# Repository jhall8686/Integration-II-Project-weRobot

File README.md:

# Integration-II-Project-weRobot
PCB FIles and Code for Autonomous Vehicle

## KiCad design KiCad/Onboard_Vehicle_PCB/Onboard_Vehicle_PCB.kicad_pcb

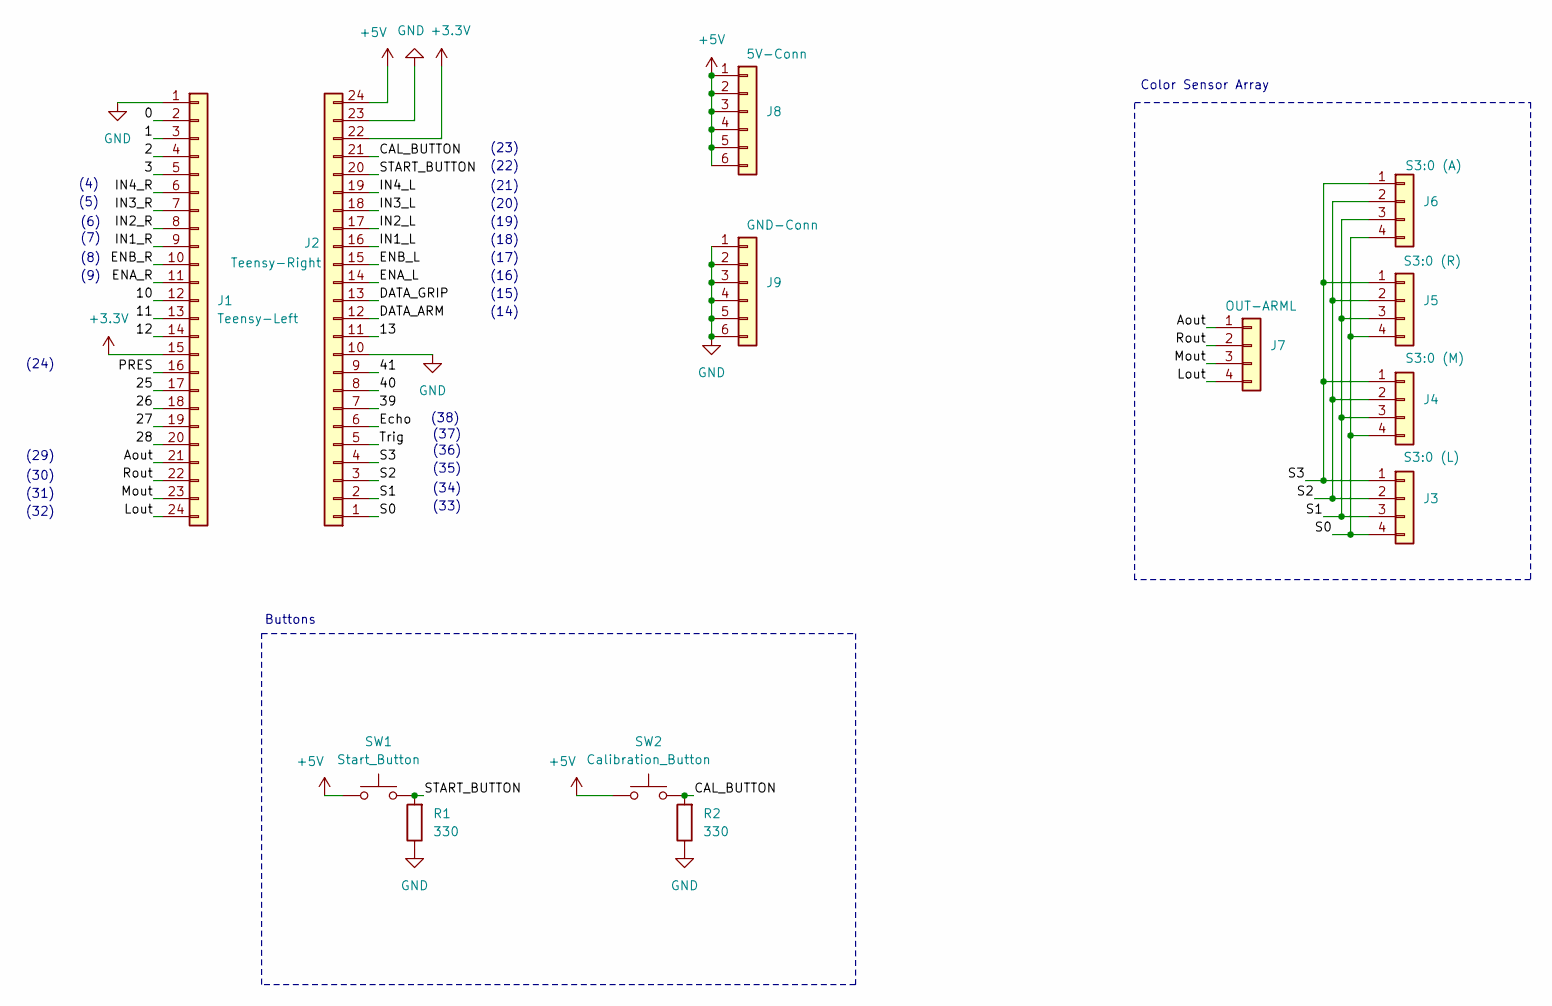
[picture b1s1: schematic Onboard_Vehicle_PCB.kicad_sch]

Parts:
J1: Teensy-Left; PinSocket_1x24_P2.54mm_Vertical
J2: Teensy-Right; PinSocket_1x24_P2.54mm_Vertical
J3: S3:0 (L); PinHeader_1x04_P2.54mm_Vertical
J4: S3:0 (M); PinHeader_1x04_P2.54mm_Vertical
J5: S3:0 (R); PinHeader_1x04_P2.54mm_Vertical
J6: S3:0 (A); PinHeader_1x04_P2.54mm_Vertical
J7: OUT-ARML; PinHeader_1x04_P2.54mm_Vertical
J8: 5V-Conn; PinHeader_1x06_P2.54mm_Vertical
J9: GND-Conn; PinHeader_1x06_P2.54mm_Vertical
R1, R2: 330; R_Axial_DIN0207_L6.3mm_D2.5mm_P10.16mm_Horizontal
SW1: Start_Button; SW_PUSH_6mm
SW2: Calibration_Button; SW_PUSH_6mm

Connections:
+3.3V: J1.15, J2.22
+5V: J2.24, J8.1, J8.2, J8.3, J8.4, J8.5, J8.6, SW1.1, SW2.1
/0: J1.2
/1: J1.3
/2: J1.4
/3: J1.5
/4: J1.6
/5: J1.7
/6: J1.8
/7: J1.9
/8: J1.10
/9: J1.11
/10: J1.12
/11: J1.13
/12: J1.14
/13: J2.11
/25: J1.17
/26: J1.18
/27: J1.19
/28: J1.20
/39: J2.7
/40: J2.8
/41: J2.9
/Aout: J1.21, J7.1
/CAL_BUTTON: J2.21, R2.2, SW2.2
/DATA_1: J2.12
/DATA_2: J2.13
/ENA: J2.14
/ENB: J2.15
/Echo: J2.6
/IN1: J2.16
/IN2: J2.17
/IN3: J2.18
/IN4: J2.19
/Lout: J1.24, J7.4
/Mout: J1.23, J7.3
/PRES: J1.16
/Rout: J1.22, J7.2
/S0: J2.1, J3.4, J4.4, J5.4, J6.4
/S1: J2.2, J3.3, J4.3, J5.3, J6.3
/S2: J2.3, J3.2, J4.2, J5.2, J6.2
/S3: J2.4, J3.1, J4.1, J5.1, J6.1
/START_BUTTON: J2.20, R1.2, SW1.2
/Trig: J2.5
GND: J1.1, J2.10, J2.23, J9.1, J9.2, J9.3, J9.4, J9.5, J9.6, R1.1, R2.1

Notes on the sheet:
(19)
(23)
(17)
(24)
(29)
(34)
(5)
(9)
(7)
(30)
(15)
(18)
Buttons
(36)
(33)
(6)
Color Sensor Array
(22)
(16)
(38)
(21)
(4)
(20)
(35)
(32)
(8)
(31)
(14)
(37)

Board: 2 copper layers, 13 parts (0 on the bottom side), 13 nets, no tracks yet.

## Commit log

2025-04-04 KiCad v1 WIP
2025-04-04 PCB v1 WIP
2025-04-25 Commit 4/25
2025-04-30 Commit 4/30-- with OOP Library Motor.h
2025-05-28 Haven't in a while
2025-06-03 6/3 Commit
2025-06-09 Final Commit
